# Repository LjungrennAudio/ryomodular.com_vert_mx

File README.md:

# ryomodular.com_vert_mx
 yet another new ryomodule - thi time the lon overdue vertmix mixer

2408302315

this is the repo for the ryodular.com vert_mx urorack format modular synth mixer module.

its been around as a prototypefor near 13 years and even visible on mod grid etc. yet never released so i guess it's about time really...

it's not much exciting am afraid - a 3 channel mixer with attenu version on each channel as well asbreakout signal option to allow just utility use without being used as a mixer.

it will  be available in ht new white panel/gold markings n pink knobs plus green leds along with the traditional ryo colourscheme too.
it should  be a pretty low price basic beginner DIY build friendly kinda module as oer ryo's traditional so far iutput so may not catch as much attention as the other new modules in the lineup but i feel c9mpelled to bring this cha[pter to closure at whatever cost the way things seem to be going. : D

if anyone cn come up with real exciting patch progaramming uses or unusuial thoughts for patch examples please tell me cos am not super inspired by thios one tbh - it's absolutely an essential you cnt do without in a system but it's not exactly the kimda thing you shout about - it just sits queitly in the corner doing it's job and eing an unsung hero of the modular ecosystem.

this will be cheap, unexciting and solid. it needs to e there as oart of the lineup but its not a weird quirky one or some kind of flagship - it just is.

202501080338 addendum

this is p much exactly the same story as the repos for the other modules of the set 'vert_mx, dp_switch, adda. brit_eq5', - i.e. it's not finished until it's finished and i aint attempting to bring order to chaos until it's all over so for now this aint gonna be sereing alotta change except for even more files being added. sorro.

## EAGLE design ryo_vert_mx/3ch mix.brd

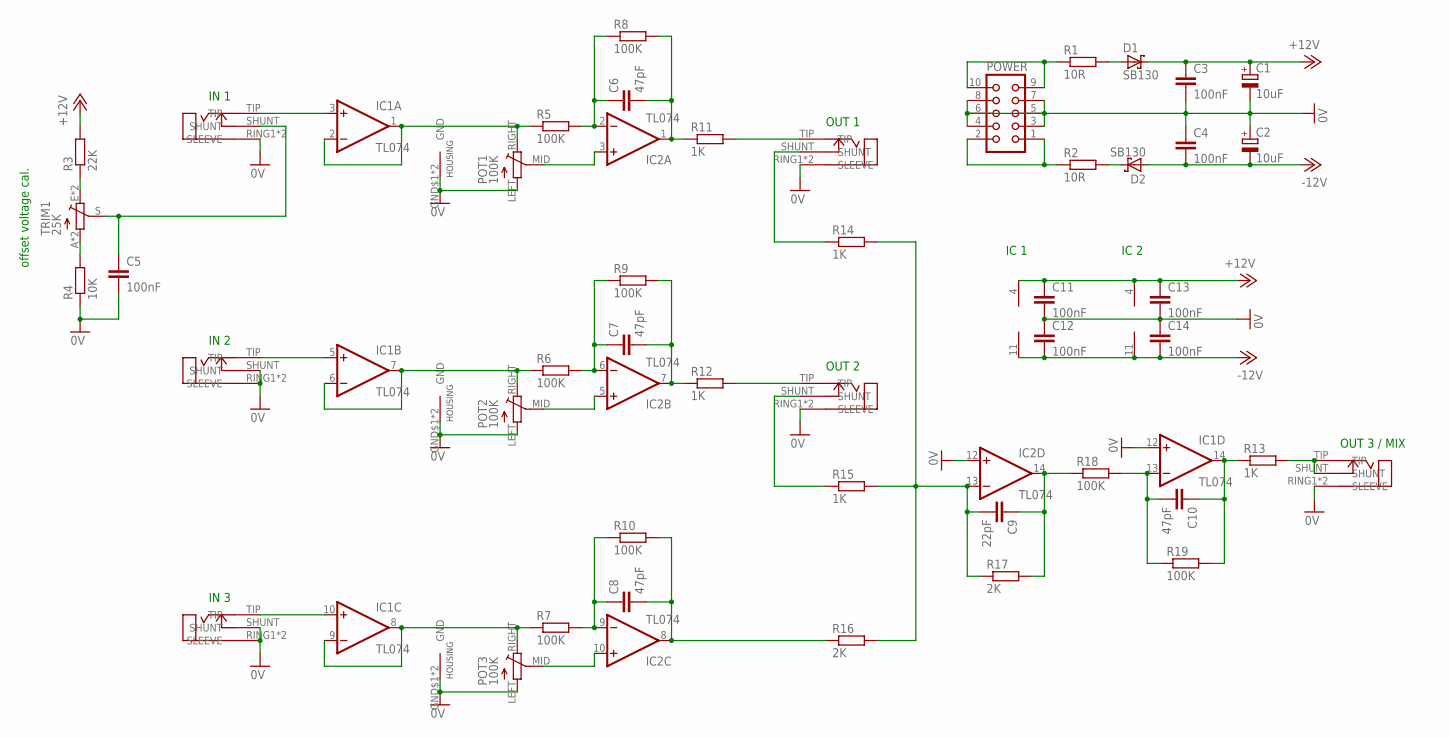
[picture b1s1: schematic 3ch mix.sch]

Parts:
C1, C2: 10uF; E2-5
C3, C4, C5, C11, C12, C13, C14: 100nF; C025-024X044
C6, C7, C8, C10: 47pF; C025-024X044
C9: 22pF; C025-024X044
D1, D2: SB130; DO41-7
IC1, IC2: TL074; DIL14
IN1, IN2, IN3: ERTHENVAR_3.5MM_JACK; ERTHENVAR
OUT1, OUT2, OUT3: ERTHENVAR_3.5MM_JACK; ERTHENVAR
POT1, POT2, POT3: 100K; POT-ALPHA9
POWER: CON10L
R1, R2: 10R; 0207/9
R3: 22K; 0207/9
R4: 10K; 0207/9
R5, R6, R7, R8, R9, R10, R18, R19: 100K; 0207/9
R11, R12, R13, R14, R15: 1K; 0207/9
R16, R17: 2K; 0207/9
TRIM1: 25K; B25P

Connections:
0V: C1.-, C2.+, C3.2, C4.1, C5.2, C11.2, C12.1, C13.2, C14.1, IC1.12 (+IN), IC2.12 (+IN), IN1.RING1 (SLEEVE), IN1.RING2 (SLEEVE), IN2.RING1 (SLEEVE), IN2.RING2 (SLEEVE), IN2.SHUNT, IN3.RING1 (SLEEVE), IN3.RING2 (SLEEVE), IN3.SHUNT, OUT1.RING1 (SLEEVE), OUT1.RING2 (SLEEVE), OUT2.RING1 (SLEEVE), OUT2.RING2 (SLEEVE), OUT3.RING1 (SLEEVE), OUT3.RING2 (SLEEVE), POT1.GND$1 (GND), POT1.GND$2 (GND), POT1.LEFT, POT2.GND$1 (GND), POT2.GND$2 (GND), POT2.LEFT, POT3.GND$1 (GND), POT3.GND$2 (GND), POT3.LEFT, POWER.3, POWER.4, POWER.5, POWER.6, POWER.7, POWER.8, R4.1
+12V: C1.+, C3.1, C11.1, C13.1, D1.C, IC1.4 (V+), IC2.4 (V+), R3.2
-12V: C2.-, C4.2, C12.2, C14.2, D2.A, IC1.11 (V-), IC2.11 (V-)
unnamed: POWER.9, POWER.10, R1.1
unnamed: POWER.1, POWER.2, R2.1
unnamed: R4.2, TRIM1.A, TRIM1.AA (A)
unnamed: D1.A, R1.2
unnamed: D2.C, R2.2
unnamed: R3.1, TRIM1.E, TRIM1.EE (E)
unnamed: C5.1, IN1.SHUNT, TRIM1.S
unnamed: IC1.3 (+IN), IN1.TIP
unnamed: IC1.5 (+IN), IN2.TIP
unnamed: IC1.10 (+IN), IN3.TIP
unnamed: IC1.1 (OUT), IC1.2 (-IN), POT1.RIGHT, R5.1
unnamed: IC1.6 (-IN), IC1.7 (OUT), POT2.RIGHT, R6.1
unnamed: IC1.8 (OUT), IC1.9 (-IN), POT3.RIGHT, R7.1
unnamed: C6.1, IC2.2 (-IN), R5.2, R8.1
unnamed: IC2.3 (+IN), POT1.MID
unnamed: IC2.5 (+IN), POT2.MID
unnamed: IC2.10 (+IN), POT3.MID
unnamed: OUT1.TIP, R11.2
unnamed: OUT2.TIP, R12.2
unnamed: C7.1, IC2.6 (-IN), R6.2, R9.1
unnamed: C8.1, IC2.9 (-IN), R7.2, R10.1
unnamed: C6.2, IC2.1 (OUT), R8.2, R11.1
unnamed: C7.2, IC2.7 (OUT), R9.2, R12.1
unnamed: C8.2, IC2.8 (OUT), R10.2, R16.1
unnamed: OUT1.SHUNT, R14.1
unnamed: OUT2.SHUNT, R15.1
unnamed: C9.2, IC2.13 (-IN), R14.2, R15.2, R16.2, R17.1
unnamed: C9.1, IC2.14 (OUT), R17.2, R18.1
unnamed: C10.2, IC1.13 (-IN), R18.2, R19.1
unnamed: C10.1, IC1.14 (OUT), R13.1, R19.2
unnamed: OUT3.SHUNT, OUT3.TIP, R13.2

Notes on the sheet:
offset voltage cal.
IN 1
IN 2
IN 3
OUT 1
OUT 2
OUT 3 / MIX
IC 1
IC 2
HOUSING

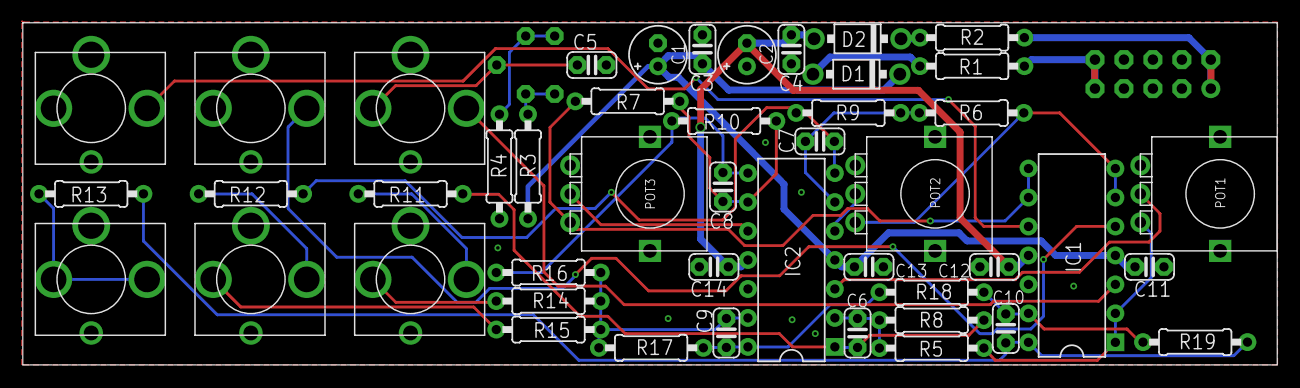
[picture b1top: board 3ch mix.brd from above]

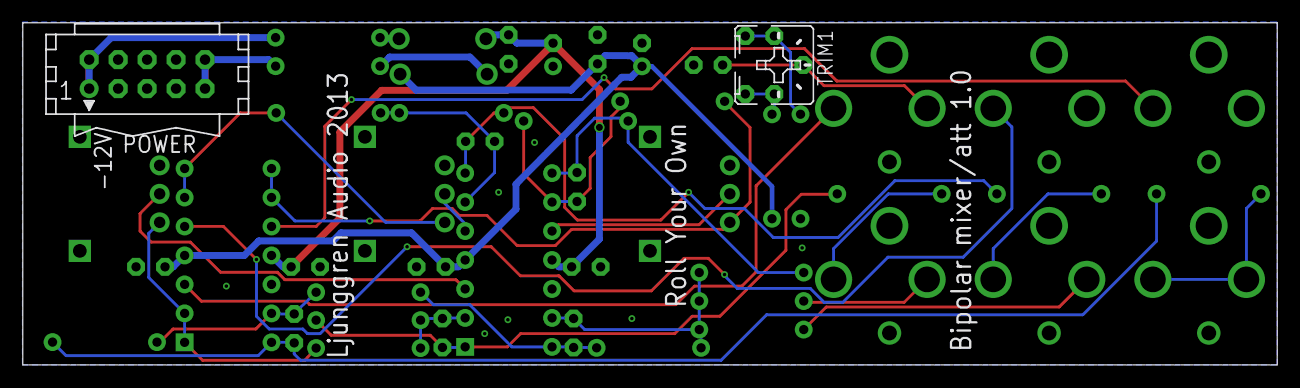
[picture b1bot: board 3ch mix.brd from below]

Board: 2 copper layers, 110.0 x 30.0 mm, 48 parts (2 on the bottom side), 34 nets.

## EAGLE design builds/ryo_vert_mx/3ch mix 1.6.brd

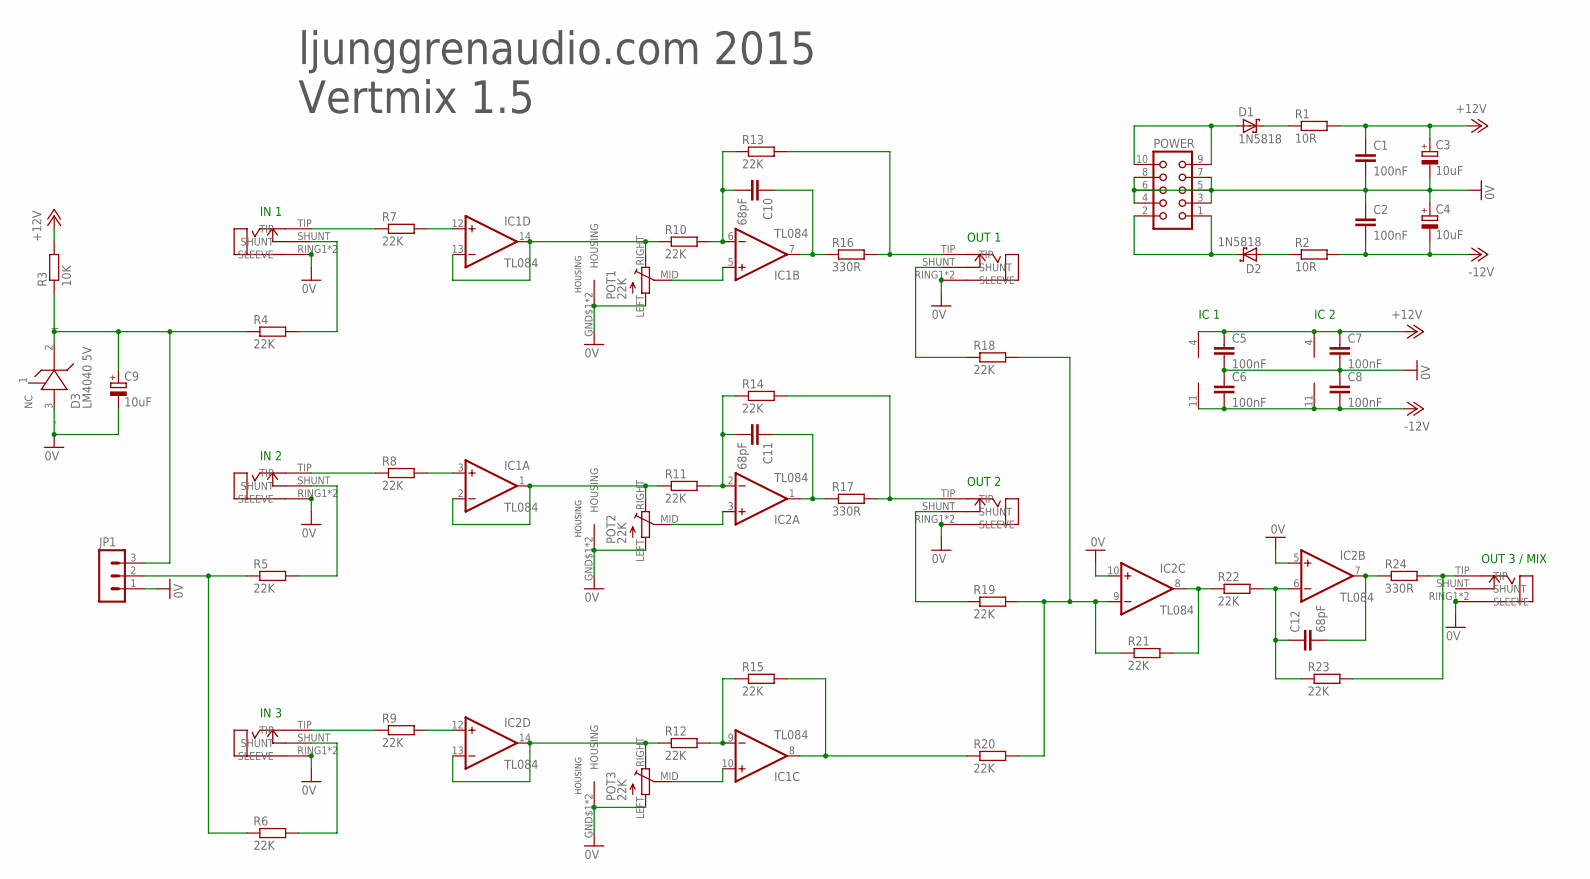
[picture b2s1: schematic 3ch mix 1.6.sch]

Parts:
C1, C2, C5, C6, C7, C8: 100nF; C0805K
C3, C4, C9: 10uF; E2-5
C10, C11, C12: 68pF; C0805K
D1, D2: 1N5818; DO41-7
D3: LM4040 5V; TO92-LINE
IC1, IC2: TL084; DIL14
IN1, IN2, IN3: ERTHENVAR_3.5MM_JACKHOLES; ERTHENVAR
JP1: MA03-1
OUT1, OUT2, OUT3: ERTHENVAR_3.5MM_JACKHOLES; ERTHENVAR
POT1, POT2, POT3: 22K; POT-ALPHA9
POWER: CON10L
R1, R2: 10R; C0805K
R3: 10K; C0805K
R4, R5, R6, R7, R8, R9, R10, R11, R12, R13, R14, R15, R18, R19, R20, R21, R22, R23: 22K; C0805K
R16, R17, R24: 330R; C0805K

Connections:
0V: C1.2, C2.1, C3.-, C4.+, C5.2, C6.1, C7.2, C8.1, C9.-, D3.3 (-), IC2.5 (+IN), IC2.10 (+IN), IN1.RING1 (SLEEVE), IN1.RING2 (SLEEVE), IN2.RING1 (SLEEVE), IN2.RING2 (SLEEVE), IN3.RING1 (SLEEVE), IN3.RING2 (SLEEVE), JP1.1, OUT1.RING1 (SLEEVE), OUT1.RING2 (SLEEVE), OUT2.RING1 (SLEEVE), OUT2.RING2 (SLEEVE), OUT3.RING1 (SLEEVE), OUT3.RING2 (SLEEVE), POT1.GND$1 (HOUSING), POT1.GND$2 (HOUSING), POT1.LEFT, POT2.GND$1 (HOUSING), POT2.GND$2 (HOUSING), POT2.LEFT, POT3.GND$1 (HOUSING), POT3.GND$2 (HOUSING), POT3.LEFT, POWER.3, POWER.4, POWER.5, POWER.6, POWER.7, POWER.8
+12V: C1.1, C3.+, C5.1, C7.1, IC1.4 (V+), IC2.4 (V+), R1.2, R3.2
-12V: C2.2, C4.-, C6.2, C8.2, IC1.11 (V-), IC2.11 (V-), R2.2
unnamed: D1.A, POWER.9, POWER.10
unnamed: D2.C, POWER.1, POWER.2
unnamed: IC2.8 (OUT), R21.2, R22.1
unnamed: C12.1, IC2.6 (-IN), R22.2, R23.1
unnamed: D1.C, R1.1
unnamed: D2.A, R2.1
unnamed: C9.+, D3.2 (+), JP1.3, R3.1, R4.1
unnamed: OUT1.TIP, R13.2, R16.2
unnamed: IC1.12 (+IN), R7.2
unnamed: IC1.3 (+IN), R8.2
unnamed: IC2.12 (+IN), R9.2
unnamed: IC1.13 (-IN), IC1.14 (OUT), POT1.RIGHT, R10.1
unnamed: IC1.1 (OUT), IC1.2 (-IN), POT2.RIGHT, R11.1
unnamed: IC2.13 (-IN), IC2.14 (OUT), POT3.RIGHT, R12.1
unnamed: C10.2, IC1.6 (-IN), R10.2, R13.1
unnamed: IC1.5 (+IN), POT1.MID
unnamed: IC2.3 (+IN), POT2.MID
unnamed: IC1.10 (+IN), POT3.MID
unnamed: OUT2.TIP, R14.2, R17.2
unnamed: IN1.TIP, R7.1
unnamed: C11.2, IC2.2 (-IN), R11.2, R14.1
unnamed: IC1.9 (-IN), R12.2, R15.1
unnamed: OUT3.TIP, R23.2, R24.2
unnamed: IN2.TIP, R8.1
unnamed: IC1.8 (OUT), R15.2, R20.1
unnamed: OUT1.SHUNT, R18.1
unnamed: OUT2.SHUNT, R19.1
unnamed: IC2.9 (-IN), R18.2, R19.2, R20.2, R21.1
unnamed: C12.2, IC2.7 (OUT), R24.1
unnamed: IN1.SHUNT, R4.2
unnamed: IN2.SHUNT, R5.2
unnamed: IN3.SHUNT, R6.2
unnamed: JP1.2, R5.1, R6.1
unnamed: IN3.TIP, R9.1
unnamed: C10.1, IC1.7 (OUT), R16.1
unnamed: C11.1, IC2.1 (OUT), R17.1

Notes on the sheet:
IN 1
IN 2
IN 3
OUT 1
OUT 2
OUT 3 / MIX
IC 1
IC 2
HOUSING
ljunggrenaudio.com 2015 Vertmix 1.5

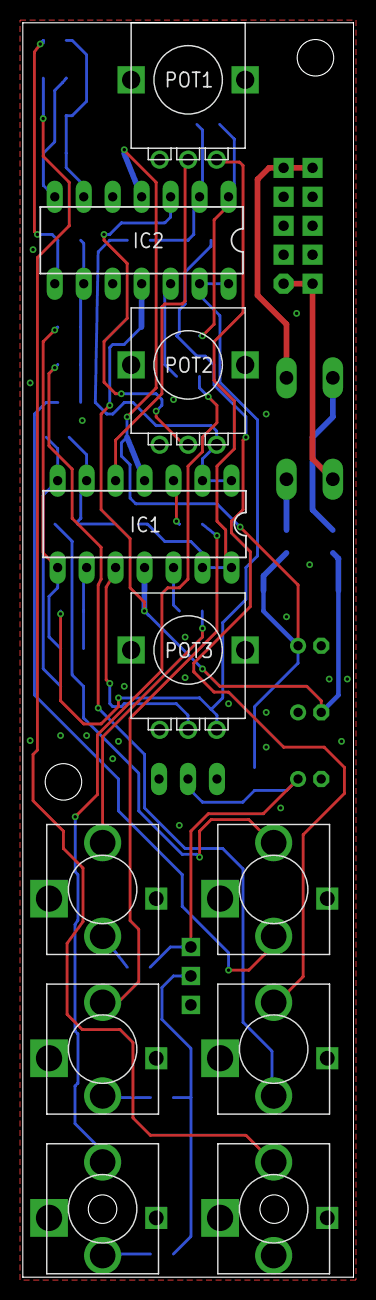
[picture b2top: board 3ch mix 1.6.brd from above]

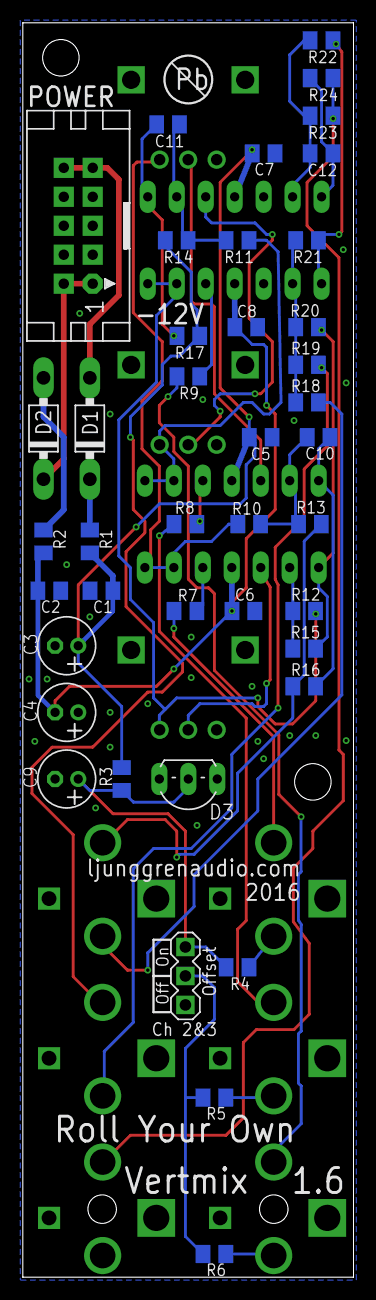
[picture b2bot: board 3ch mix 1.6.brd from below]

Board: 2 copper layers, 29.0 x 110.0 mm, 52 parts (41 on the bottom side), 39 nets.

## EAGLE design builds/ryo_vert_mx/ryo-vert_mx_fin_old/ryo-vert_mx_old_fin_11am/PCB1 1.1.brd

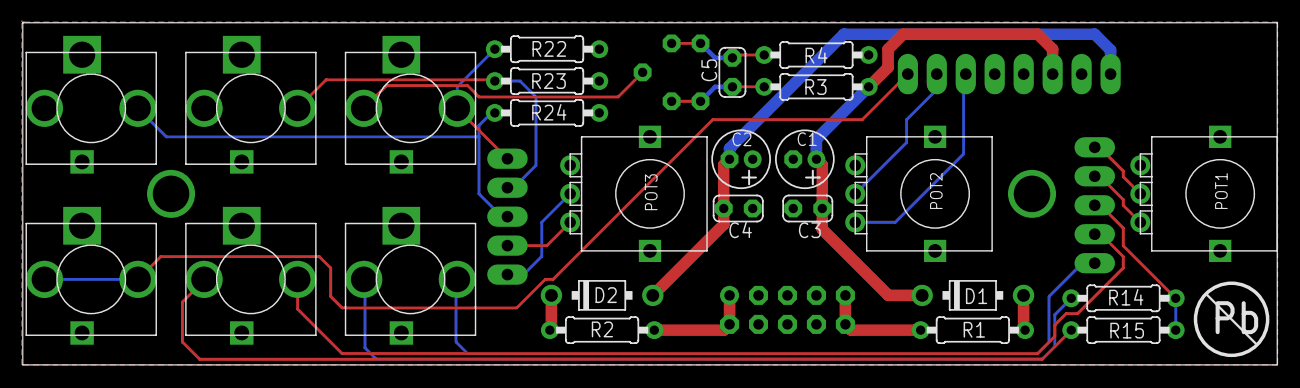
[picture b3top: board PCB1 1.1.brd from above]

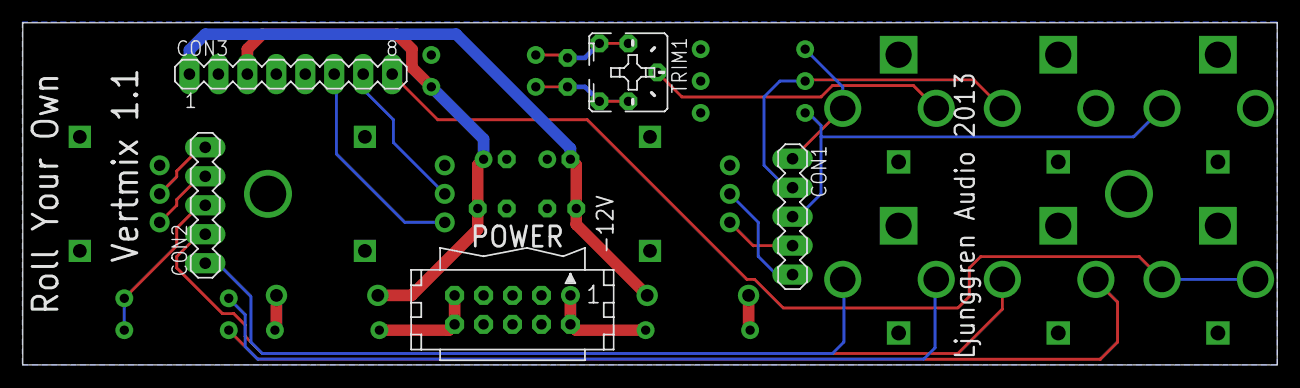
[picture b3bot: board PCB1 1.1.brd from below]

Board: 2 copper layers, 110.0 x 30.0 mm, 30 parts (5 on the bottom side), 25 nets.

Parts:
C1, C2: 10uF; E2-5
C3, C4, C5: 100nF; C025-024X044
CON1, CON2: MA05-1
CON3: MA08-1
D1, D2: SB130; DO41-7
IN1, IN2, IN3: ERTHENVAR_3.5MM_JACK; ERTHENVAR
OUT1, OUT2, OUT3: ERTHENVAR_3.5MM_JACK; ERTHENVAR
POT1, POT2, POT3: 100K; POT-ALPHA9
POWER: CON10L
R1, R2: 10R; 0207/9
R3, R4: 2.2K; 0207/9
R14, R15: 100K; 0207/9
R22, R23, R24: 1M; 0207/9
TRIM1: 25K; B25P

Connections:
0V: C1.-, C2.+, C3.2, C4.1, CON3.2, CON3.4, CON3.5, IN1.RING1, IN1.RING2, IN2.RING1, IN2.RING2, IN2.SHUNT, IN3.RING1, IN3.RING2, IN3.SHUNT, OUT1.RING1, OUT1.RING2, OUT2.RING1, OUT2.RING2, OUT3.RING1, OUT3.RING2, POT1.GND$1, POT1.GND$2, POT1.LEFT, POT2.GND$1, POT2.GND$2, POT2.LEFT, POT3.GND$1, POT3.GND$2, POT3.LEFT, POWER.3, POWER.4, POWER.5, POWER.6, POWER.7, POWER.8, R4.1, R22.2, R23.2, R24.2
+12V: C1.+, C3.1, CON3.3, D1.C, R3.2
-12V: C2.-, C4.2, CON3.1, D2.A
unnamed: POWER.9, POWER.10, R1.1
unnamed: POWER.1, POWER.2, R2.1
unnamed: C5.2, R4.2, TRIM1.A, TRIM1.AA
unnamed: D1.A, R1.2
unnamed: D2.C, R2.2
unnamed: C5.1, R3.1, TRIM1.E, TRIM1.EE
unnamed: IN1.SHUNT, TRIM1.S
unnamed: CON1.1, IN1.TIP, R22.1
unnamed: CON1.2, IN2.TIP, R23.1
unnamed: CON1.3, IN3.TIP, R24.1
unnamed: CON2.1, OUT1.TIP
unnamed: CON2.2, OUT2.TIP
unnamed: OUT1.SHUNT, R14.1
unnamed: OUT2.SHUNT, R15.1
unnamed: CON2.3, R14.2, R15.2
OUT: CON3.8, OUT3.SHUNT, OUT3.TIP
POT1M: CON2.5, POT1.MID
POT1R: CON2.4, POT1.RIGHT
POT2M: CON3.7, POT2.MID
POT2R: CON3.6, POT2.RIGHT
POT3M: CON1.5, POT3.MID
POT3R: CON1.4, POT3.RIGHT

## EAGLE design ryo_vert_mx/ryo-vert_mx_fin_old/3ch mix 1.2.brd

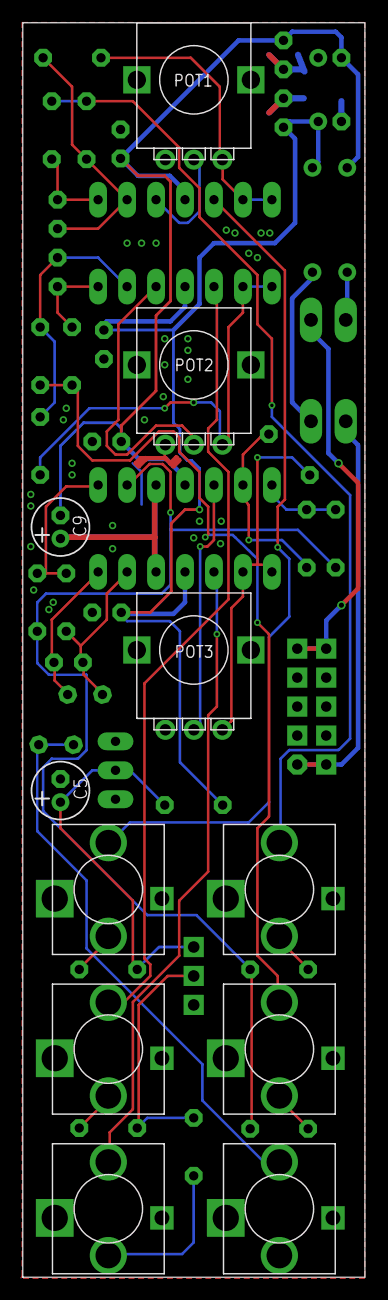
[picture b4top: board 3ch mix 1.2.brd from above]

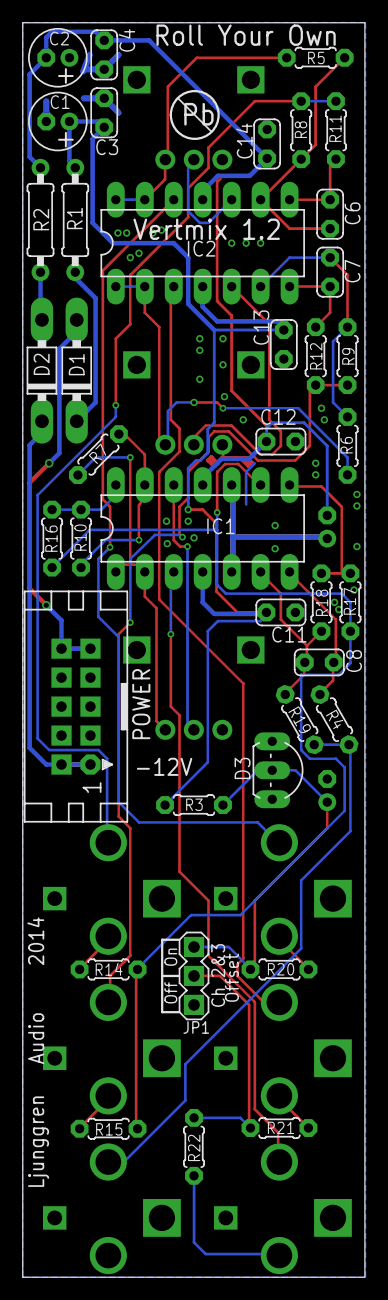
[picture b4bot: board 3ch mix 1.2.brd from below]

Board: 2 copper layers, 30.0 x 110.0 mm, 50 parts (39 on the bottom side), 36 nets.

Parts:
C1, C2, C5, C9: 10uF; E2-5
C3, C4, C11, C12, C13, C14: 100nF; C025-024X044
C6, C7, C8: 68pF; C025-024X044
D1, D2: SB130; DO41-7
D3: LM4040 5V; TO92-LINE
IC1, IC2: TL074; DIL14
IN1, IN2, IN3: ERTHENVAR_3.5MM_JACK; ERTHENVAR
JP1: MA03-1
OUT1, OUT2, OUT3: ERTHENVAR_3.5MM_JACK; ERTHENVAR
POT1, POT2, POT3: 22K; POT-ALPHA9
POWER: CON10L
R1, R2: 10R; 0207/9
R3: 10K; 0204/5
R4, R11, R12: 330R; 0204/5
R5, R6, R7, R8, R9, R10, R14, R15, R16, R17, R18, R19, R20, R21, R22: 22K; 0204/5

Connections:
0V: C1.-, C2.+, C3.2, C4.1, C5.-, C9.+, C11.2, C12.1, C13.2, C14.1, D3.3, IC1.5, IC1.10, IN1.RING1, IN1.RING2, IN2.RING1, IN2.RING2, IN3.RING1, IN3.RING2, JP1.1, OUT1.RING1, OUT1.RING2, OUT2.RING1, OUT2.RING2, OUT3.RING1, OUT3.RING2, POT1.GND$1, POT1.GND$2, POT1.LEFT, POT2.GND$1, POT2.GND$2, POT2.LEFT, POT3.GND$1, POT3.GND$2, POT3.LEFT, POWER.3, POWER.4, POWER.5, POWER.6, POWER.7, POWER.8
+12V: C1.+, C3.1, C11.1, C13.1, IC1.4, IC2.4, R1.2, R3.2
-12V: C2.-, C4.2, C9.-, C12.2, C14.2, IC1.11, IC2.11, R2.2
unnamed: D1.A, POWER.9, POWER.10
unnamed: D2.C, POWER.1, POWER.2
unnamed: IC1.8, R17.2, R18.1
unnamed: C8.1, IC1.6, R18.2, R19.1
unnamed: D1.C, R1.1
unnamed: D2.A, R2.1
unnamed: C5.+, D3.2, JP1.3, R3.1, R20.1
unnamed: C6.1, IC2.8, R11.1
unnamed: IC2.12, IN1.TIP
unnamed: IC2.3, IN2.TIP
unnamed: IC1.3, IN3.TIP
unnamed: IC2.13, IC2.14, POT1.RIGHT, R5.1
unnamed: IC2.1, IC2.2, POT2.RIGHT, R6.1
unnamed: IC1.1, IC1.2, POT3.RIGHT, R7.1
unnamed: C6.2, IC2.9, R5.2, R8.1
unnamed: IC2.10, POT1.MID
unnamed: IC2.5, POT2.MID
unnamed: IC1.12, POT3.MID
unnamed: OUT1.TIP, R8.2, R11.2
unnamed: OUT2.TIP, R9.2, R12.2
unnamed: C7.2, IC2.6, R6.2, R9.1
unnamed: IC1.13, R7.2, R10.1
unnamed: OUT3.TIP, R4.2, R19.2
unnamed: C7.1, IC2.7, R12.1
unnamed: IC1.14, R10.2, R16.1
unnamed: OUT1.SHUNT, R14.1
unnamed: OUT2.SHUNT, R15.1
unnamed: IC1.9, R14.2, R15.2, R16.2, R17.1
unnamed: C8.2, IC1.7, R4.1
unnamed: IN1.SHUNT, R20.2
unnamed: IN2.SHUNT, R21.2
unnamed: IN3.SHUNT, R22.2
unnamed: JP1.2, R21.1, R22.1

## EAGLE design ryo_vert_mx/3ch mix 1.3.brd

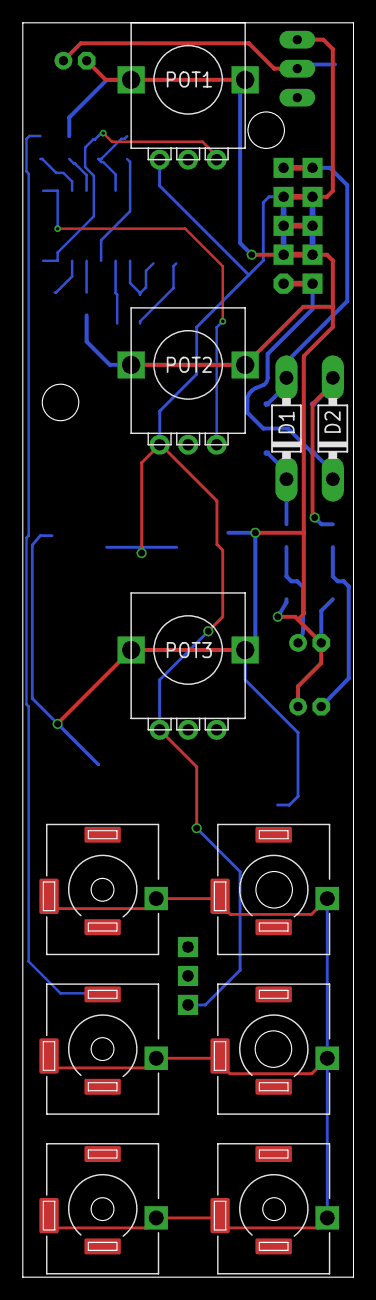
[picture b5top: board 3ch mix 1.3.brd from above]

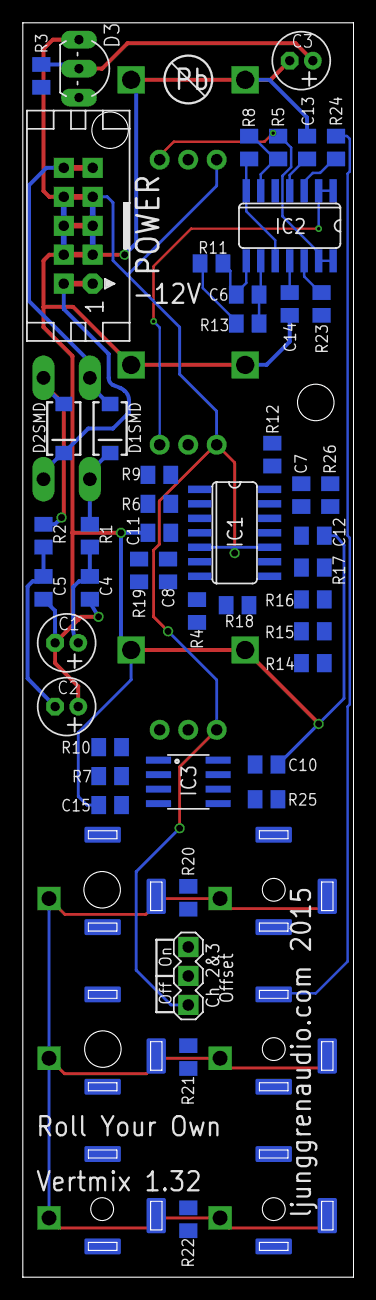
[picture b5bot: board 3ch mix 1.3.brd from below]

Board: 2 copper layers, 29.0 x 110.0 mm, 59 parts (48 on the bottom side), 43 nets.

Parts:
C1, C2, C3: 10uF; E2-5
C4, C5, C10, C11, C12, C13, C14, C15: 100nF; C0805K
C6, C7, C8: 68pF; C0805K
D1, D2: 1N5818; DO41-7
D1SMD, D2SMD: B140; SMA-DIODE
D3: LM4040 5V; TO92-LINE
IC1, IC2: TL084; SO14
IC3: TL072D; SO08
IN1, IN2, IN3: ERTHENVAR_3.5MM_JACKSLOTS; ERTHENVAR-SLOTS
JP1: MA03-1
OUT1, OUT2, OUT3: ERTHENVAR_3.5MM_JACKSLOTS; ERTHENVAR-SLOTS
POT1, POT2, POT3: 22K; POT-ALPHA9
POWER: CON10L
R1, R2: 10R; C0805K
R3, R23, R24, R25: 10K; C0805K
R4, R11, R12: 330R; C0805K
R5, R6, R7, R8, R9, R10, R13, R14, R15, R16, R17, R18, R19, R20, R21, R22, R26: 22K; C0805K

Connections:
0V: C1.-, C2.+, C3.-, C4.2, C5.1, C10.2, C11.2, C12.1, C13.2, C14.1, C15.1, D3.3, IC1.5, IC1.10, IN1.RING1B, IN1.RING1T, IN1.RING2H, IN2.RING1B, IN2.RING1T, IN2.RING2H, IN3.RING1B, IN3.RING1T, IN3.RING2H, JP1.1, OUT1.RING1B, OUT1.RING1T, OUT1.RING2H, OUT2.RING1B, OUT2.RING1T, OUT2.RING2H, OUT3.RING1B, OUT3.RING1T, OUT3.RING2H, POT1.GND$1, POT1.GND$2, POT1.LEFT, POT2.GND$1, POT2.GND$2, POT2.LEFT, POT3.GND$1, POT3.GND$2, POT3.LEFT, POWER.3, POWER.4, POWER.5, POWER.6, POWER.7, POWER.8
+12V: C1.+, C4.1, C10.1, C11.1, C13.1, IC1.4, IC2.4, IC3.8, R1.2, R3.2
-12V: C2.-, C5.2, C12.2, C14.2, C15.2, IC1.11, IC2.11, IC3.4, R2.2
unnamed: D1.A, D1SMD.A, POWER.9, POWER.10
unnamed: D2.C, D2SMD.C, POWER.1, POWER.2
unnamed: IC1.8, R17.2, R18.1
unnamed: C8.1, IC1.6, R18.2, R19.1
unnamed: D1.C, D1SMD.C, R1.1
unnamed: D2.A, D2SMD.A, R2.1
unnamed: C3.+, D3.2, JP1.3, R3.1, R20.1
unnamed: IC2.7, IC2.10, R8.2
unnamed: IC2.12, R23.2
unnamed: IC2.3, R24.2
unnamed: IC3.5, R25.2
unnamed: IC2.13, IC2.14, POT1.RIGHT, R5.1
unnamed: IC2.1, IC2.2, POT2.RIGHT, R6.1
unnamed: IC3.6, IC3.7, POT3.RIGHT, R7.1
unnamed: IC2.6, R5.2, R8.1
unnamed: IC2.5, POT1.MID
unnamed: IC1.3, POT2.MID
unnamed: IC3.3, POT3.MID
unnamed: IC1.1, IC1.12, R9.2
unnamed: IN1.TIPB, IN1.TIPT, R23.1
unnamed: IC1.2, R6.2, R9.1
unnamed: IC3.2, R7.2, R10.1
unnamed: OUT3.TIPB, OUT3.TIPT, R4.2, R19.2
unnamed: IN2.TIPB, IN2.TIPT, R24.1
unnamed: IC3.1, R10.2, R16.1
unnamed: OUT1.NORMLB, OUT1.NORMLT, R14.1
unnamed: OUT2.NORMLB, OUT2.NORMLT, R15.1
unnamed: IC1.9, R14.2, R15.2, R16.2, R17.1
unnamed: C8.2, IC1.7, R4.1
unnamed: IN1.NORMLB, IN1.NORMLT, R20.2
unnamed: IN2.NORMLB, IN2.NORMLT, R21.2
unnamed: IN3.NORMLB, IN3.NORMLT, R22.2
unnamed: JP1.2, R21.1, R22.1
unnamed: IN3.TIPB, IN3.TIPT, R25.1
unnamed: C6.2, IC2.9, R13.1
unnamed: OUT1.TIPB, OUT1.TIPT, R11.2, R13.2
unnamed: C6.1, IC2.8, R11.1
unnamed: C7.1, IC1.14, R12.1
unnamed: OUT2.TIPB, OUT2.TIPT, R12.2, R26.2
unnamed: C7.2, IC1.13, R26.1

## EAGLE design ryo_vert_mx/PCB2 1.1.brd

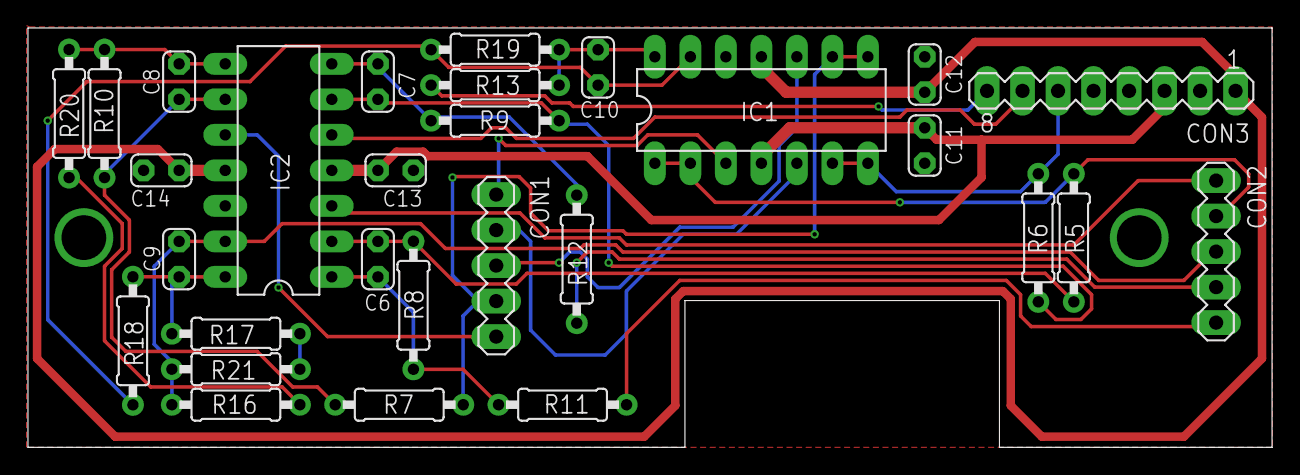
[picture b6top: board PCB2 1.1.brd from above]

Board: 2 copper layers, 89.0 x 30.0 mm, 29 parts (0 on the bottom side), 27 nets.

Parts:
C6, C7, C8, C9, C10: 47pF; C025-024X044
C11, C12, C13, C14: 100nF; C025-024X044
CON1, CON2: MA05-1
CON3: MA08-1
IC1, IC2: TL074; DIL14
R5, R6, R7, R8, R9, R10, R16, R17, R18, R19: 100K; 0207/9
R11, R12, R13, R20, R21: 1K; 0207/9

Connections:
0V: C11.2, C12.1, C13.2, C14.1, CON3.2, CON3.4, CON3.5, IC1.12, IC2.12
+12V: C11.1, C13.1, CON3.3, IC1.4, IC2.4
-12V: C12.2, C14.2, CON3.1, IC1.11, IC2.11
unnamed: R16.1, R20.2
unnamed: CON1.1, IC1.3
unnamed: CON1.2, IC1.5
unnamed: CON1.3, IC1.10
unnamed: C6.1, IC2.2, R5.2, R8.1
unnamed: CON2.1, R11.2
unnamed: CON2.2, R12.2
unnamed: C7.1, IC2.6, R6.2, R9.1
unnamed: C8.1, IC2.9, R7.2, R10.1
unnamed: C6.2, IC2.1, R8.2, R11.1
unnamed: C7.2, IC2.7, R9.2, R12.1
unnamed: C8.2, IC2.8, R10.2, R20.1
unnamed: R17.1, R21.1
unnamed: C9.1, IC2.14, R17.2, R18.1
unnamed: C10.2, IC1.13, R18.2, R19.1
unnamed: C10.1, IC1.14, R13.1, R19.2
unnamed: C9.2, CON2.3, IC2.13, R16.2, R21.2
OUT: CON3.8, R13.2
POT1M: CON2.5, IC2.3
POT1R: CON2.4, IC1.1, IC1.2, R5.1
POT2M: CON3.7, IC2.5
POT2R: CON3.6, IC1.6, IC1.7, R6.1
POT3M: CON1.5, IC2.10
POT3R: CON1.4, IC1.8, IC1.9, R7.1

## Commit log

2024-08-30 init commit or ryomldular.com vert_mx
    as usual the init commit is a mess of random unsorted carnage that eventually gets cleaned and tidied and generally sorted into a pro[er project poeple can make sense of...
2024-09-06 added a coupla files i guess
2024-09-29 create vert_mx gerbers.zip
    shop asked for repeats /shrug
2024-10-02 tidying up mess from init commit
    just filing things away into neat lil folders
2024-11-05 only promo after this
    can tidy up soon
2024-12-23 blue dot
    blu
2025-01-07 new crap added npow it's released and fuinally off my radar
    good to see end of this - now i can tidy this gitinto a comprhensible state
2025-01-08 t i d y
    omg for realz
2025-01-12 added docs
2025-01-13 wow a lotta stuff
    dunno what
2025-01-13 filing

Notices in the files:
parts and their libraries:
SparkFun-DiscreteSemi: Licensing: Creative Commons ShareAlike 4.0 International - https://creativecommons.org/licenses/by-sa/4.0
